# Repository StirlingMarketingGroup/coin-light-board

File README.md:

# Coin Light Board

A small circuit board that goes inside a metal challenge coin. Press the button and a red light and a blue light flash in turn, like a police light. Press again and the lights stop.

**Back side.** This side faces the back of the coin. It has the batteries, the chip, and the button.

**Front side.** This side faces the front of the coin. It has the two LEDs. Each LED sits under one light window of the coin.

## Status

**Revision C. Designed, not built.** The layout passes KiCad's design-rule check and the firmware compiles. No board has been made or tested yet.

Revision A was a first test layout. It is kept under the git tag `rev-a`.

## What it does

- Press the button: red is on for 250 ms, then blue is on for 250 ms. This repeats. That is 2 cycles each second.
- Press the button again: both lights turn off.
- After 60 seconds the lights turn off on their own. This saves the battery if a coin is left on.
- When the lights are off, the chip sleeps and uses almost no power.

## Size and fit

| | |
| --- | --- |
| Board | 75 mm long, 22 mm wide |
| Button tab | 12.4 mm wide. It goes 5.4 mm below the middle of the board. |
| Screw tabs | 2 tabs, each with one hole for an M2 screw. They go 4.6 mm below the long edge. |
| Screw holes | 2.2 mm wide, 25 mm apart, 24.2 mm from the straight edge |
| Height with batteries | about 6 mm (estimate) |
| Batteries | 2 × CR2032 |
| Lights | 1 red LED and 1 blue LED, on the front side |
| Distance between the LEDs | 67.5 mm, center to center |
| Button | 6 mm × 6 mm push button, on the back side |

The board is sized for the sample coin. The coin is 95.47 mm long and 34.15 mm wide. The space inside it is 90.96 mm long and 30.05 mm wide.

**Lights.** No wires are needed. The red LED and the blue LED are on the front side of the board, 67.5 mm apart. Put the board in the coin so that each LED is under the middle of a light window. The front side is marked `RED` and `BLUE`.

**Button.** The button is on the back side, on the small tab. Its stem goes through a hole in the back of the coin. The button comes with stems of different heights. Choose the height after the thickness of the coin's back is known.

**Screws.** Two M2 screws hold the board in the coin. One hole is 21.5 mm from the left end of the board and one is 46.5 mm from it, seen from the back side. The coin needs a post under each hole.

**Batteries.** Each holder has a `+` mark. Put each battery in with its `+` side up, facing away from the board.

## The circuit

**Why two batteries.** A red LED needs about 2 V. A blue LED needs about 3 V. One 3 V coin battery is not enough for the blue LED when the battery gets older. Two batteries in series give 6 V for the LEDs. The chip uses only the lower battery, so the board needs no voltage regulator.

**Why two transistors.** Each LED has its own transistor and its own resistor. A red LED and a blue LED that share one output do not both light, because the red LED holds the voltage too low for the blue one.

## Parts

| Ref | Part | Side | JLCPCB part | Note |
| --- | --- | --- | --- | --- |
| U1 | ATtiny202-SSNR, SOIC-8 | Back | C2052951 | ATtiny402, 212 and 412 fit the same pads and run the same firmware. |
| Q1, Q2 | MMBT3904, SOT-23 | Back | C20526 | |
| R3, R4 | 10 kΩ, 0603 | Back | C25804 | Confirm the part number on JLCPCB. |
| C1 | 100 nF, 0603 | Back | C14663 | Confirm the part number on JLCPCB. |
| R1 | 820 Ω, 0603 | Back | C23253 | Sets the red brightness, about 5 mA. |
| R2 | 620 Ω, 0603 | Back | C23220 | Sets the blue brightness, about 5 mA. |
| SW1 | TS-1102S-C-C-B push button, 6 × 6 × 5 mm | Back | C381039 | 5 mm tall for the test. The final height depends on the thickness of the coin's back. |
| BT1, BT2 | MY-2032-08-R CR2032 holder | Back | C964832 | |
| D1 | NCD0805R1 red LED, 0805 | Front | C84256 | |
| D2 | KT-0805B blue LED, 0805 | Front | C2293 | |

Parts are on both sides, so the order needs JLCPCB's Standard assembly service. The cheaper Economic service places one side only. [ORDERING.md](ORDERING.md) lists every choice for the order.

## Files

| File | What it is |
| --- | --- |
| `pcb/coin-light-board.kicad_pcb` | The board. Open it in KiCad 10. |
| `pcb/build_board.py` | The script that draws the board. Every part position and trace is listed in it. |
| `pcb/export.sh` | Rebuilds the board, checks it, and writes the factory files. |
| `pcb/coin-light-board-gerbers.zip` | Gerber and drill files for the bare board. |
| `pcb/jlcpcb-bom.csv`, `pcb/jlcpcb-cpl.csv` | Parts list and placement file for JLCPCB assembly. |
| `pcb/lib.pretty/` | The battery holder and button footprints, from JLCPCB's own library. |
| `ORDERING.md` | How to order test boards from JLCPCB, step by step. |
| `firmware/firmware.hex` | The compiled firmware, ready to load onto the chip. |
| `firmware/src/main.c` | The firmware, about 60 lines of C. |
| `firmware/build.sh` | Compiles the firmware in Docker. |

## Build

Firmware, with Docker running:

```sh
firmware/build.sh
```

The file for the chip is `firmware/firmware.hex`. Load it through the `UPDI`, `3V` and `GND` pads on the front side with a UPDI programmer. **Take both batteries out first.** A programmer that powers the `3V` pad would push current into the lower battery.

Board files, with KiCad 10 in `~/Applications/KiCad`:

```sh
pcb/export.sh
```

## Known gaps

- Nothing has been built. The LED resistor values come from calculation. They need tuning on a real board.
- The depth of the space inside the coin is not known yet. Thinner batteries (CR2025 or CR2016) use the same circuit if 6 mm is too much.
- The lower battery also runs the chip, so it drains a little faster than the upper one while the lights flash.
- If something holds the button down, the chip sleeps, but its pull-up resistor still draws about 0.1 mA. That would empty the lower battery in about three months.
- Nothing protects the board from a battery put in upside down.
- No trace runs under a battery on the back side. The rim of a coin cell is its `+` side, so only solder mask may sit under it.
- There is no schematic file. The circuit drawing above and `build_board.py` are the design.
- The positions and rotations in the JLCPCB placement file may need correcting in JLCPCB's preview, most of all for the two LEDs on the front side.

## License

MIT. See [LICENSE](LICENSE). The board design and the firmware are both covered.

## Made by

[Signature Coins](https://signaturecoins.com), a Stirling Marketing Group brand.

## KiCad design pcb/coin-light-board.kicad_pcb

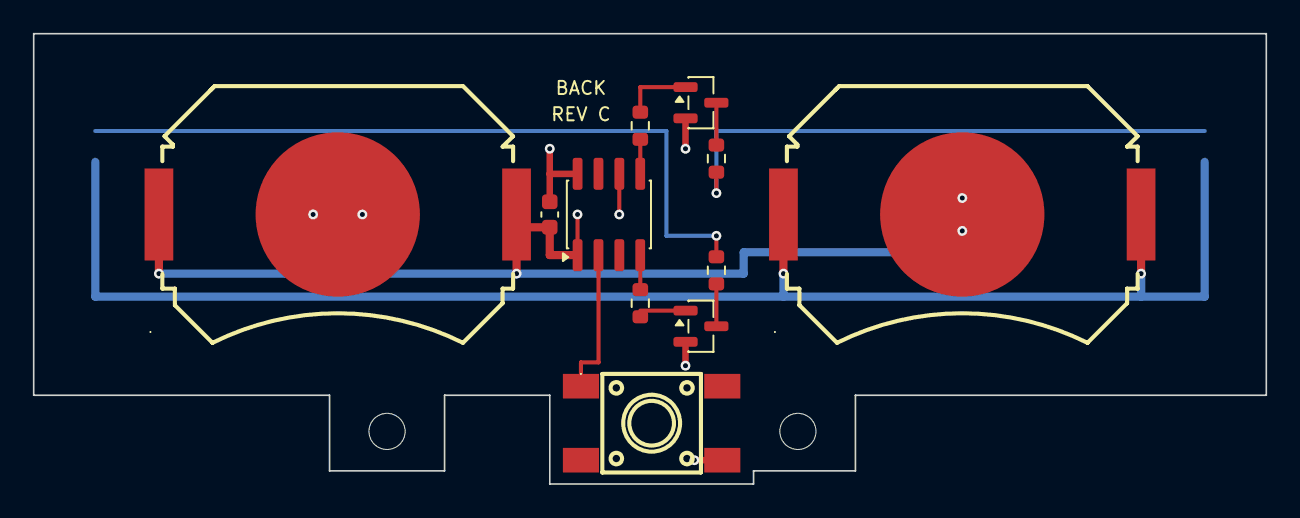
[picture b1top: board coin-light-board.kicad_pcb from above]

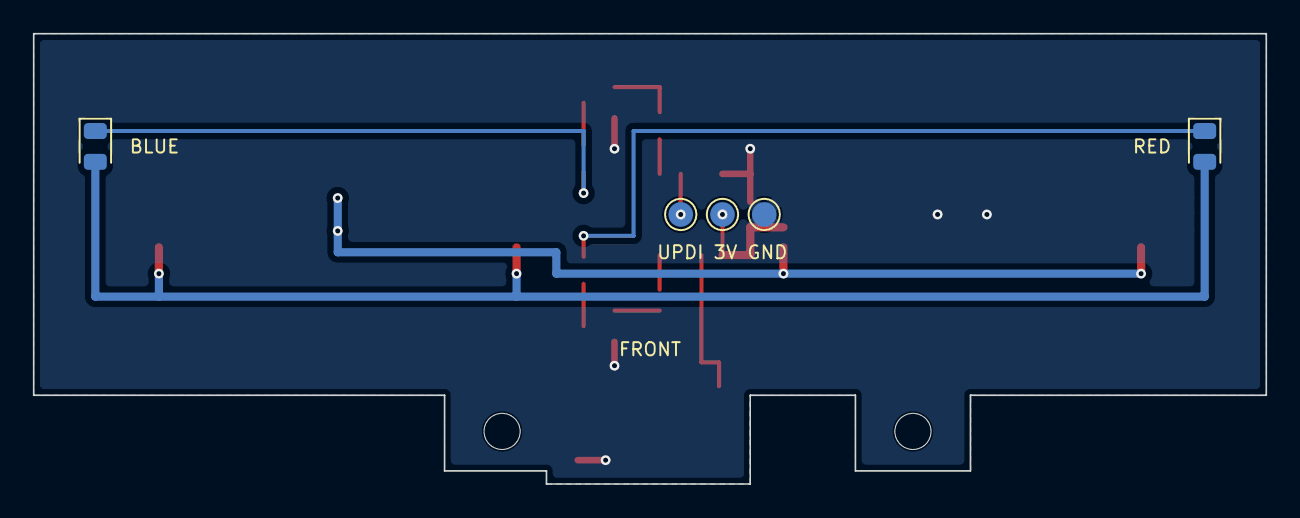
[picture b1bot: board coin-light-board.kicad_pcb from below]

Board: 2 copper layers, 75.0 x 27.4 mm, 18 parts (5 on the bottom side), 13 nets.

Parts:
BT1, BT2: CR2032; BAT-SMD_MY-2032-08
C1: 100nF; C_0603_1608Metric
D1: red; LED_0805_2012Metric
D2: blue; LED_0805_2012Metric
H1, H2: M2; MountingHole_2.2mm_M2
Q1, Q2: MMBT3904; SOT-23
R1: 820; R_0603_1608Metric
R2: 620; R_0603_1608Metric
R3, R4: 10k; R_0603_1608Metric
SW1: 6x6 tact; KEY-SMD_4P-L6.0-W6.0-P4.50-LS8.6
TP1: GND; TestPoint_Pad_D1.5mm
TP2: VDD; TestPoint_Pad_D1.5mm
TP3: UPDI; TestPoint_Pad_D1.5mm
U1: ATtiny202; SOIC-8_3.9x4.9mm_P1.27mm

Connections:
B1: Q1.1, R3.2
B2: Q2.1, R4.2
BK: D2.1, R2.1
BTN: SW1.1, U1.2
C1: Q1.3, R1.1
C2: Q2.3, R2.2
GND: BT1.2, C1.2, Q1.2, Q2.2, SW1.4, TP1.1, U1.8
PA1: R3.1, U1.4
PA2: R4.1, U1.5
RK: D1.1, R1.2
UPDI: TP3.1, U1.6
VLED: BT2.1, D1.2, D2.2
VMID: BT1.1, BT2.2, C1.1, TP2.1, U1.1

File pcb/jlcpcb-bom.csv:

Comment,Designator,Footprint,LCSC Part #
ATtiny202-SSNR,U1,SOIC-8,C2052951
MMBT3904,"Q1,Q2",SOT-23,C20526
10k 0603,"R3,R4",0603,C25804
820R 0603,R1,0603,C23253
620R 0603,R2,0603,C23220
100nF 0603,C1,0603,C14663
Red LED 0805 NCD0805R1,D1,0805,C84256
Blue LED 0805 KT-0805B,D2,0805,C2293
Push button 6x6x5mm TS-1102S-C-C-B,SW1,SMD 6x6,C381039
CR2032 holder MY-2032-08-R,"BT1,BT2",SMD,C964832

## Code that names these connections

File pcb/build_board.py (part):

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    # Upper cell, stacked on the lower one. Its + tabs are the 6 V LED rail.
    "BT2": (BACK, HOLDER, "CR2032", 56.5, 11.0, 0, {"1": "VLED", "2": "VMID"}),
    "U1": (BACK, ("Package_SO", "SOIC-8_3.9x4.9mm_P1.27mm"), "ATtiny202", 35.0, 11.0, 90,
           {"1": "VMID", "2": "BTN", "4": "PA1", "5": "PA2", "6": "UPDI", "8": "GND"}),
    "C1": (BACK, ("Capacitor_SMD", "C_0603_1608Metric"), "100nF", 31.4, 11.0, 90,
           {"1": "VMID", "2": "GND"}),
    # Blue channel, above the chip.
    "R4": (BACK, RES, "10k", 36.91, 5.6, 90, {"1": "PA2", "2": "B2"}),
    "Q2": (BACK, NPN, "MMBT3904", 40.6, 4.2, 0, {"1": "B2", "2": "GND", "3": "C2"}),
    "R2": (BACK, RES, "620", 41.54, 7.6, 90, {"1": "BK", "2": "C2"}),
    # Red channel, below the chip.
    "R3": (BACK, RES, "10k", 36.91, 16.4, 270, {"1": "PA1", "2": "B1"}),
    "Q1": (BACK, NPN, "MMBT3904", 40.6, 17.8, 0, {"1": "B1", "2": "GND", "3": "C1"}),
    "R1": (BACK, RES, "820", 41.54, 14.4, 90, {"1": "C1", "2": "RK"}),
    # 6 x 6 mm push button on the tab. Its stem height is chosen to reach
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    ("GND", BACK, GND_W, [(39.66, 18.75), (39.66, 20.2)]),
    ("GND", BACK, GND_W, [(41.9, 25.95), (40.2, 25.95)]),
    # Blue channel.
    ("PA2", BACK, SIGNAL_W, [(36.91, 8.53), (36.91, 6.42)]),
    ("B2", BACK, SIGNAL_W, [(36.91, 4.78), (36.91, 3.25), (39.66, 3.25)]),
    ("C2", BACK, SIGNAL_W, [(41.54, 4.2), (41.54, 6.78)]),
    ("BK", BACK, SIGNAL_W, [(41.54, 8.42), (41.54, 9.7)]),
    ("BK", FRONT, SIGNAL_W, [(41.54, 9.7), (41.54, LED_K_Y), (BLUE_X, LED_K_Y)]),
    # Red channel.
    ("PA1", BACK, SIGNAL_W, [(36.91, 13.47), (36.91, 15.58)]),
    ("B1", BACK, SIGNAL_W, [(36.91, 16.85), (39.66, 16.85)]),
    ("C1", BACK, SIGNAL_W, [(41.54, 17.8), (41.54, 15.22)]),
    ("RK", BACK, SIGNAL_W, [(41.54, 13.58), (41.54, 12.3)]),
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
